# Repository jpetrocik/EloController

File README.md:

EloController is an open source  replacement for the controller for your eBike. The project was created simply out of a hobbyist interest. The goal of the project is to get to a point where the controller achieves the goal set out below.    

The design separates the main logic, aka BCU, and brushless DC driver.  Many semiconductor manufacturers are now creating dedicated chip for brushless dc motor controlling, so instead of focusing on trapezoidal, sinusoidal and field-oriented control software let a dedicate chip handle that, and with the time saved spent making the users experience better. Currently, the board uses the JYQD DC Brushless Motor Controller as a daughter board for controlling the motor.  This board is available on eBay and Amazon for about $15.  The board is rated up to 500W when using a heat sink.

Unique to the EloController is the use of the HC-05 bluetooth module to provide connectivity between your smart phone and bike.  All important data is streamed to the phone using a messaging protocol, analogous to CANBus message, the system used by modern cars to connect all the different computer modules. The EloControler acts a the BCU, or Bike Control Unit similar to a modern car's ECU.  All peripheral plug into the BCU and the BCU stream data over bluetooth to your smart phone.  Information like bike speed, hub speed, brake on/off, battery level, etc are streamed and display on your phone, no need for a separate display on the the handle bars.  Additionally the phone can send message back to the BCU for configuration setting and for features like disabling the motor, equivalent to a digital lock.  

Current Status:

* Individual modules are tested and the design is confirmed.
* PCB Design complete

Next Steps:
* Order PCB
* Solder up PCB
* Install and Test

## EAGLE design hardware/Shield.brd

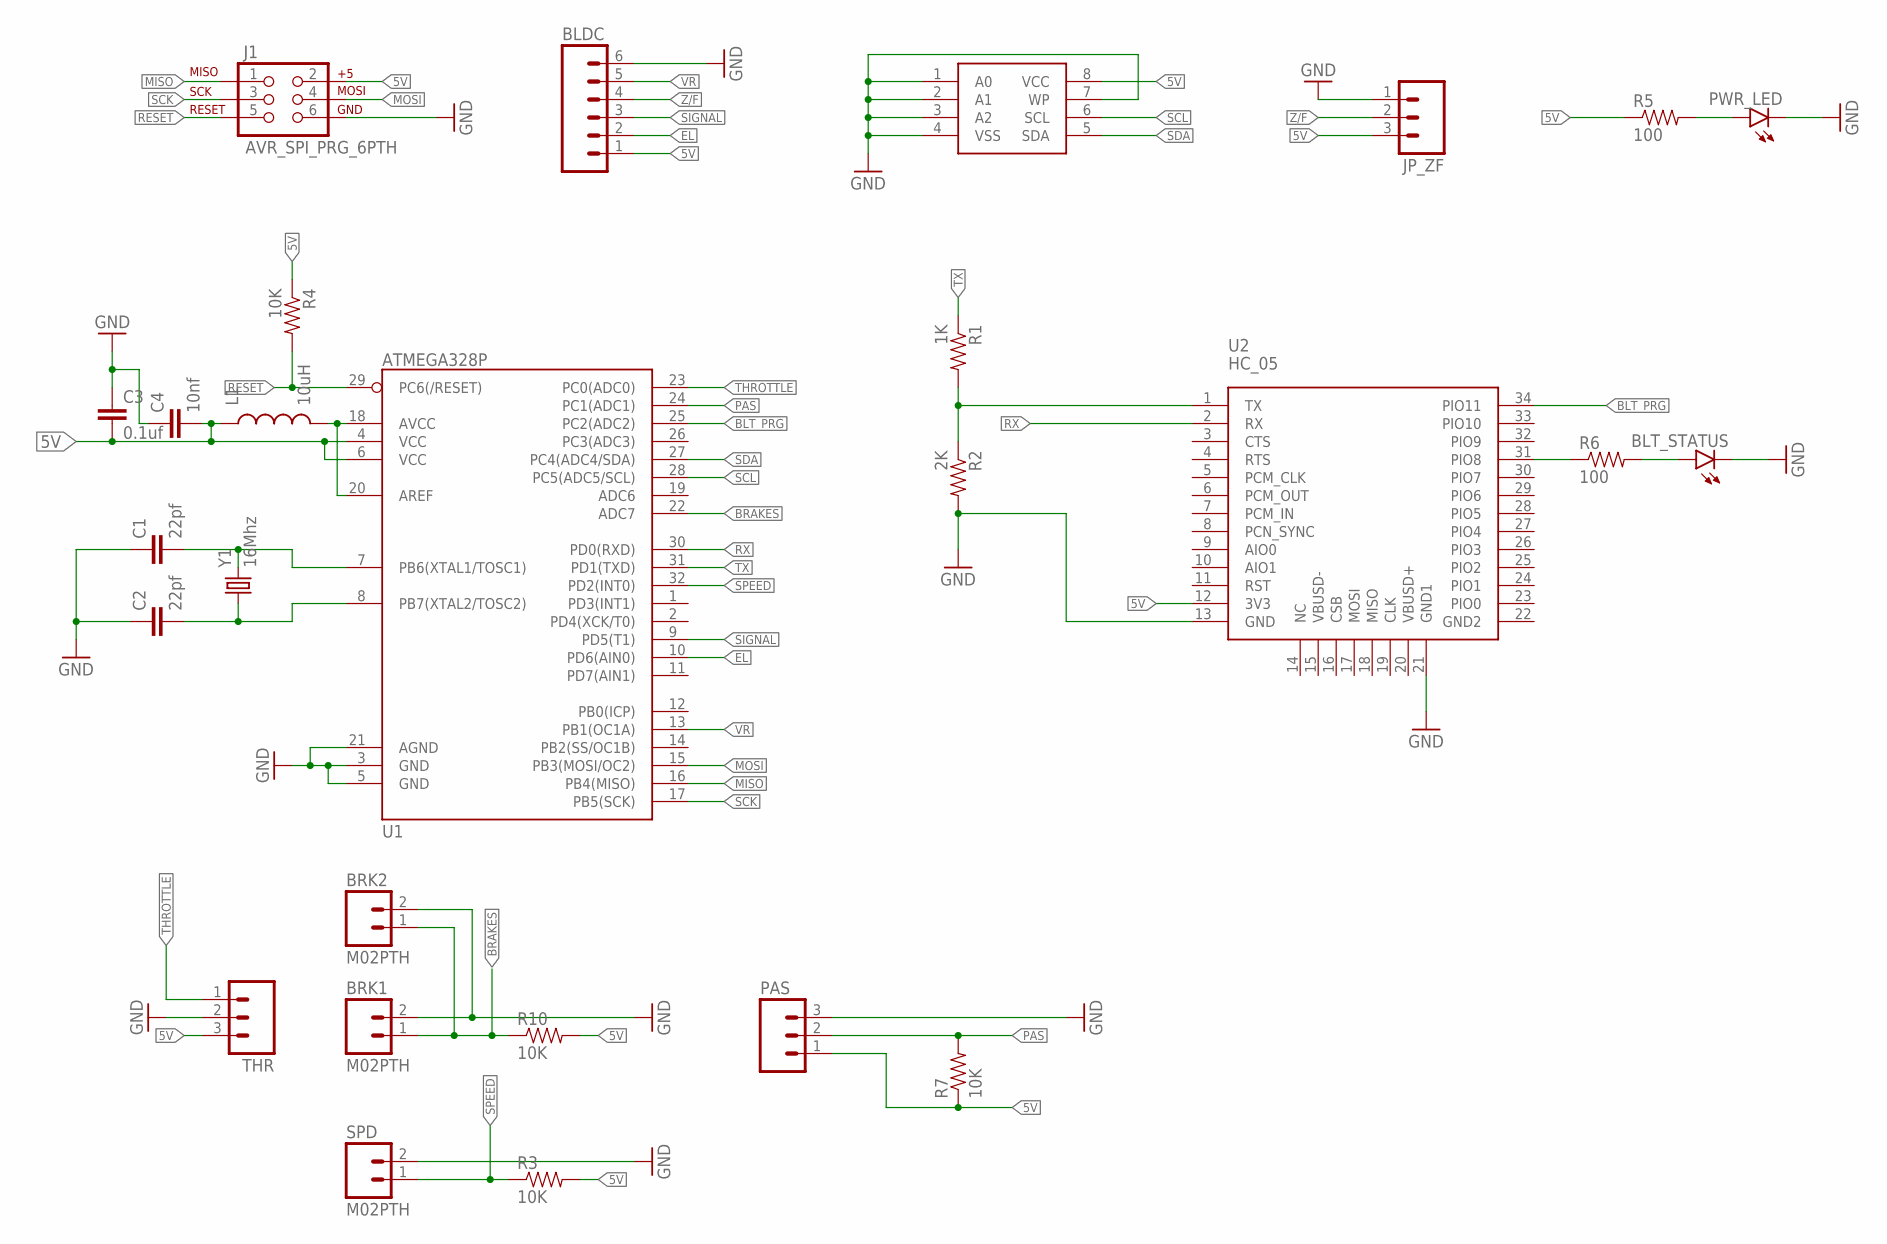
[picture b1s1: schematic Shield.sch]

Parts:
BLDC: M06NO_SILK_FEMALE_PTH; 1X06_NO_SILK
BLT_STATUS: LED1206; LED-1206
BRK1, BRK2: M02PTH; 1X02
C1, C2: 22pf; 1206
C3: 0.1uf; 1206
C4: 10nf; 1206
J1: AVR_SPI_PRG_6PTH; 2X3
JP_ZF: M03PTH; 1X03
L1: 10uH; 0805
PAS: M03PTH; 1X03
PWR_LED: LED1206; LED-1206
R1: 1K; 1206
R2: 2K; 1206
R3, R4, R7, R10: 10K; 1206
R5, R6: 100; 1206
SPD: M02PTH; 1X02
THR: M03PTH; 1X03
U1: ATMEGA328P; TQFP32-08
U2: HC_05; BLUETOOTH_SMD
U$2: 24AAXXX; SOIC-8-EIAJ
Y1: 16Mhz; HC49US

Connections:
5V: BLDC.1, C3.2, C4.2, J1.2, JP_ZF.3, L1.1, PAS.1, R3.2, R4.1, R5.1, R7.1, R10.2, THR.3, U1.4 (VCC), U1.6 (VCC), U2.12 (3V3), U$2.8 (VCC)
BLT_PRG: U1.25 (PC2(ADC2)), U2.34 (PIO11)
BRAKES: BRK1.1, BRK2.1, R10.1, U1.22 (ADC7)
EL: BLDC.2, U1.10 (PD6(AIN0))
GND: BLDC.6, BLT_STATUS.C, BRK1.2, BRK2.2, C1.1, C2.1, C3.1, C4.1, J1.6, JP_ZF.1, PAS.3, PWR_LED.C, R2.2, SPD.2, THR.2, U1.3 (GND), U1.5 (GND), U1.21 (AGND), U2.13 (GND), U2.21 (GND1), U$2.1 (A0), U$2.2 (A1), U$2.3 (A2), U$2.4 (VSS), U$2.7 (WP)
MISO: J1.1, U1.16 (PB4(MISO))
MOSI: J1.4, U1.15 (PB3(MOSI/OC2))
unnamed: R1.2, R2.1, U2.1 (TX)
unnamed: PWR_LED.A, R5.2
unnamed: R6.1, U2.31 (PIO8)
unnamed: BLT_STATUS.A, R6.2
unnamed: L1.2, U1.18 (AVCC), U1.20 (AREF)
unnamed: C1.2, U1.7 (PB6(XTAL1/TOSC1)), Y1.2
unnamed: C2.2, U1.8 (PB7(XTAL2/TOSC2)), Y1.1
PAS: PAS.2, R7.2, U1.24 (PC1(ADC1))
RESET: J1.5, R4.2, U1.29 (PC6(/RESET))
RX: U1.30 (PD0(RXD)), U2.2 (RX)
SCK: J1.3, U1.17 (PB5(SCK))
SCL: U1.28 (PC5(ADC5/SCL)), U$2.6 (SCL)
SDA: U1.27 (PC4(ADC4/SDA)), U$2.5 (SDA)
SIGNAL: BLDC.3, U1.9 (PD5(T1))
SPEED: R3.1, SPD.1, U1.32 (PD2(INT0))
THROTTLE: THR.1, U1.23 (PC0(ADC0))
TX: R1.1, U1.31 (PD1(TXD))
VR: BLDC.5, U1.13 (PB1(OC1A))
Z/F: BLDC.4, JP_ZF.2

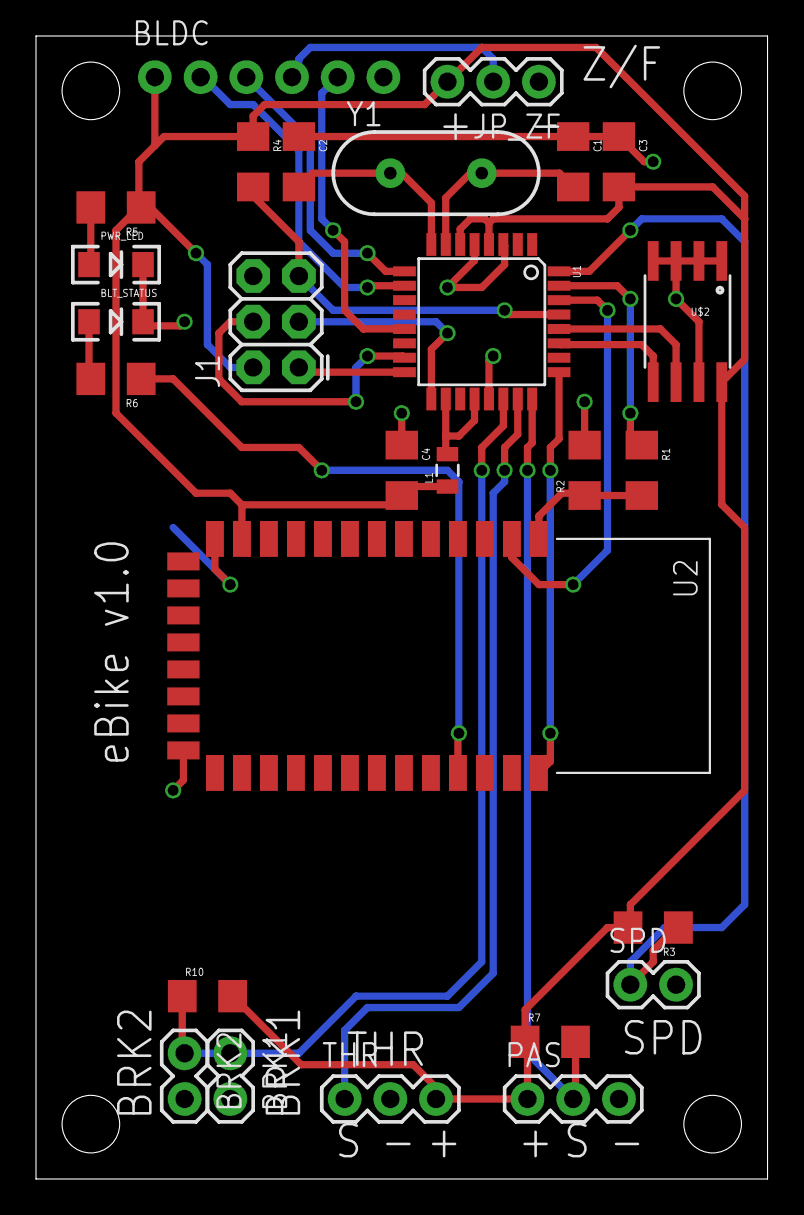
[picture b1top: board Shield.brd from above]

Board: 2 copper layers, 40.6 x 63.5 mm, 27 parts (0 on the bottom side), 26 nets.

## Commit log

2019-10-28 Inital commit
2019-10-28 Adding README.md
2019-10-28 Adding images

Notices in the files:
parts and their libraries:
SparkFun-Passives: Licensing: CC v3.0 Share-Alike You are welcome to use this library for commercial purposes.
SparkFun-DigitalIC: Licensing: Creative Commons ShareAlike 4.0 International - https://creativecommons.org/licenses/by-sa/4.0
